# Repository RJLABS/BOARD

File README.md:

# BOARD
Scematic and  PCB board repo

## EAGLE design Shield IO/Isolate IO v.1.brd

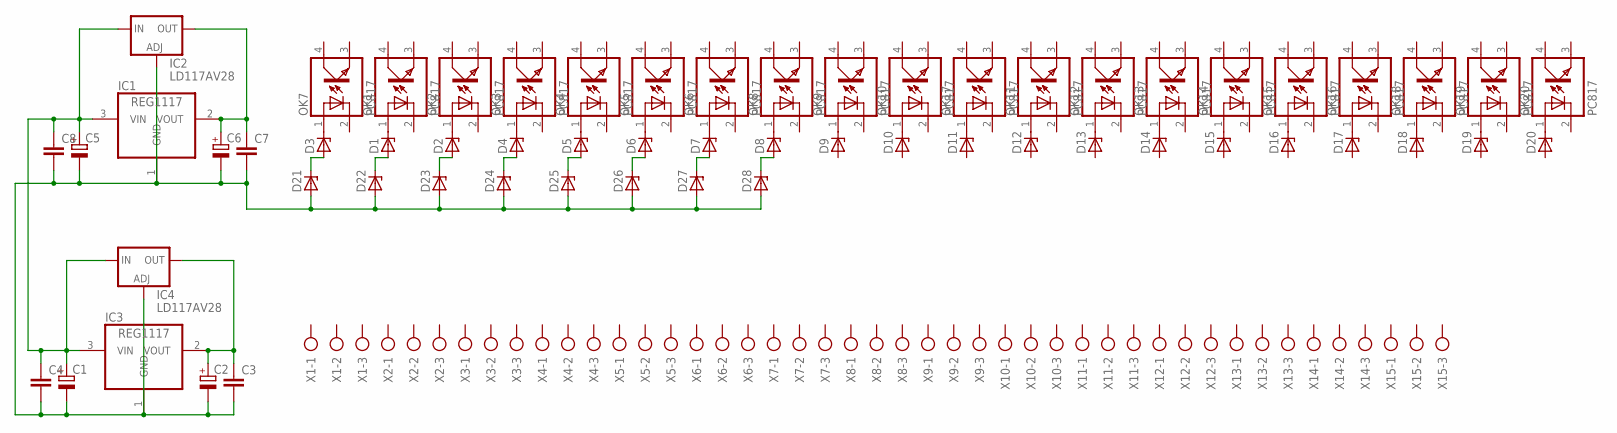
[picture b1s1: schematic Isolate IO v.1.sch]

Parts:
C1, C5: CPOL-EUE2.5-5; E2,5-5
C2, C6: CPOL-EUE3.5-10; E3,5-10
C3, C4, C7, C8: C-EU025-030X050; C025-030X050
D1, D2, D3, D4, D5, D6, D7, D8, D9, D10, D11, D12, D13, D14, D15, D16, D17, D18, D19, D20, D21, D22, D23, D24, D25, D26, D27, D28: ZENER-DIODEZD-2.5; ZDIO-2.5
IC1, IC3: REG1117; SOT223
IC2, IC4: LD117AV28; TO220L1
OK1, OK2, OK3, OK4, OK5, OK6, OK7, OK8, OK9, OK10, OK11, OK12, OK13, OK14, OK15, OK16, OK17, OK18, OK19, OK20: PC817; DIL04
X1, X2, X3, X4, X5, X6, X7, X8, X9, X10, X11, X12, X13, X14, X15: AK500/3

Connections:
unnamed: D3.C, OK7.1 (A)
unnamed: C2.+, C3.1, IC3.2 (VOUT), IC4.2 (OUT)
unnamed: D1.C, OK1.1 (A)
unnamed: C1.-, C2.-, C3.2, C4.2, C5.-, C6.-, C7.2, C8.2, D21.A, D22.A, D23.A, D24.A, D25.A, D26.A, D27.A, D28.A, IC1.1 (GND), IC2.1 (ADJ), IC3.1 (GND), IC4.1 (ADJ)
unnamed: C6.+, C7.1, IC1.2 (VOUT), IC2.2 (OUT)
unnamed: C1.+, C4.1, C5.+, C8.1, IC1.3 (VIN), IC2.3 (IN), IC3.3 (VIN), IC4.3 (IN)
unnamed: D2.C, OK2.1 (A)
unnamed: D4.C, OK3.1 (A)
unnamed: D5.C, OK4.1 (A)
unnamed: D6.C, OK5.1 (A)
unnamed: D7.C, OK6.1 (A)
unnamed: D8.C, OK8.1 (A)
unnamed: D9.C, OK9.1 (A)
unnamed: D10.C, OK10.1 (A)
unnamed: D11.C, OK17.1 (A)
unnamed: D12.C, OK11.1 (A)
unnamed: D13.C, OK12.1 (A)
unnamed: D14.C, OK13.1 (A)
unnamed: D15.C, OK14.1 (A)
unnamed: D16.C, OK15.1 (A)
unnamed: D17.C, OK16.1 (A)
unnamed: D18.C, OK18.1 (A)
unnamed: D19.C, OK19.1 (A)
unnamed: D20.C, OK20.1 (A)
unnamed: D3.A, D21.C
unnamed: D1.A, D22.C
unnamed: D2.A, D23.C
unnamed: D4.A, D24.C
unnamed: D5.A, D25.C
unnamed: D6.A, D26.C
unnamed: D7.A, D27.C
unnamed: D8.A, D28.C

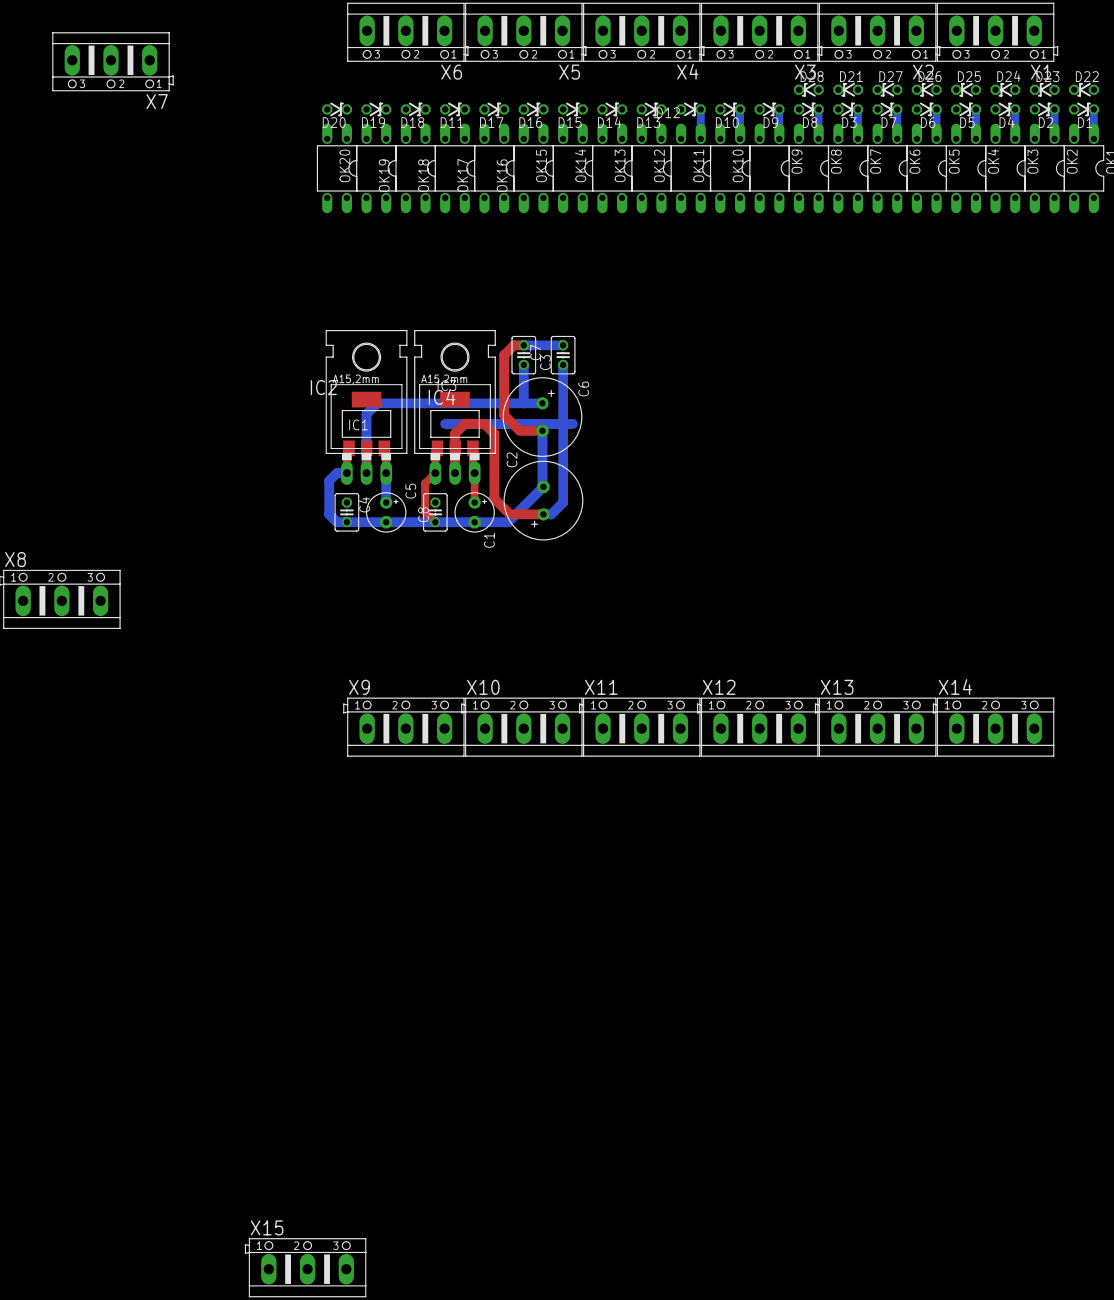
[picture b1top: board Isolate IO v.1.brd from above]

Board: 2 copper layers, 75 parts (0 on the bottom side), 32 nets.

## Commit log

2019-02-11 addprojek isolated sield
2019-02-11 add reference design pdf
